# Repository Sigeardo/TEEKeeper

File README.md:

**TEEKeeper** (_Temperature Environment Electronic Keeper_, or _TEEK_ for short) is an open source, Arduino based controller for high temperature electric ovens, such as heat treating ovens for metallurgy/bladesmithing, glass and ceramic kilns, etc.
In a broader sense, this projects aims to develop a platform that can be upgraded, expanded and extended by anyone, bringing more advanced control features to the users.

# Project principles
This university & passion project has been developed with 5 principles in mind:

**1) Open Source and DIY oriented design:**
     TEEK has been inspired by and made possible by many open source and DIY sources, in the forms of documentation, educational material, tools, software, designs etc.
     This project embraces these principles and aspires to give something back to these communities.

**2) Safety and Security:**
     Both in the design of the code and the circuits, developing methods & functions keeping in mind the potential risks for the user.

**3) Accessibility & ease of use:**
     The system may grow more and more complex, but the user must be presented with a simple, undestrandable and intuitive U/I.
     The code must be as readable as possible, to allow anyone to approach the codebase to make 

**4) It doesn't stop at the board:**
     Data logging and analysis tools can help to improve workflows and perform diagnostics checks. Give users data collection methods, statistics and tools.

**6) Be creative & don't be afraid of complexity!**
     But still, try to keep it simple - not trivial!
     
***DISCLAIMER: high temperature & electric related hazards are very real. 
Be aware of what you're doing and use this code at your own risk.***

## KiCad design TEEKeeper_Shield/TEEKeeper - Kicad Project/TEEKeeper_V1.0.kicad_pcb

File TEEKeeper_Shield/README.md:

# TEEKeeper Shield

**TEEKeeper** (_Temperature Environment Electronic Keeper_, or _TEEK_ for short) is an open source, Arduino based controller for high temperature electric ovens, such as heat treating ovens for metallurgy/bladesmithing, glass and ceramic kilns, etc.
In a broader sense, this projects aims to develop a platform that can be upgraded, expanded and extended by anyone, bringing more advanced control features to the users.

This branch contains the KiCad & Gerber source files for the TEEKeeper Shield circuit. The main components are:
> [Arduino Mega2560](https://docs.arduino.cc/hardware/mega-2560/)

> [Adafruit MAX31855K temperature sensor](https://www.adafruit.com/product/269)

> SD card reader w/ 8 pin interface [(example)](https://europe1.discourse-cdn.com/arduino/original/4X/2/f/4/2f487c179e937e868c1862e275f90aaaed0d1cb2.jpeg)

> 3.5" TFT 480x320px ILI9486/HX8357 Screen Mega Shield [LCDWIKI](http://www.lcdwiki.com/3.5inch_Arduino_Display-Mega2560)

> Normally open door switch

> Rotary encoder with push button [Aliexpress](https://it.aliexpress.com/i/32920789846.html)

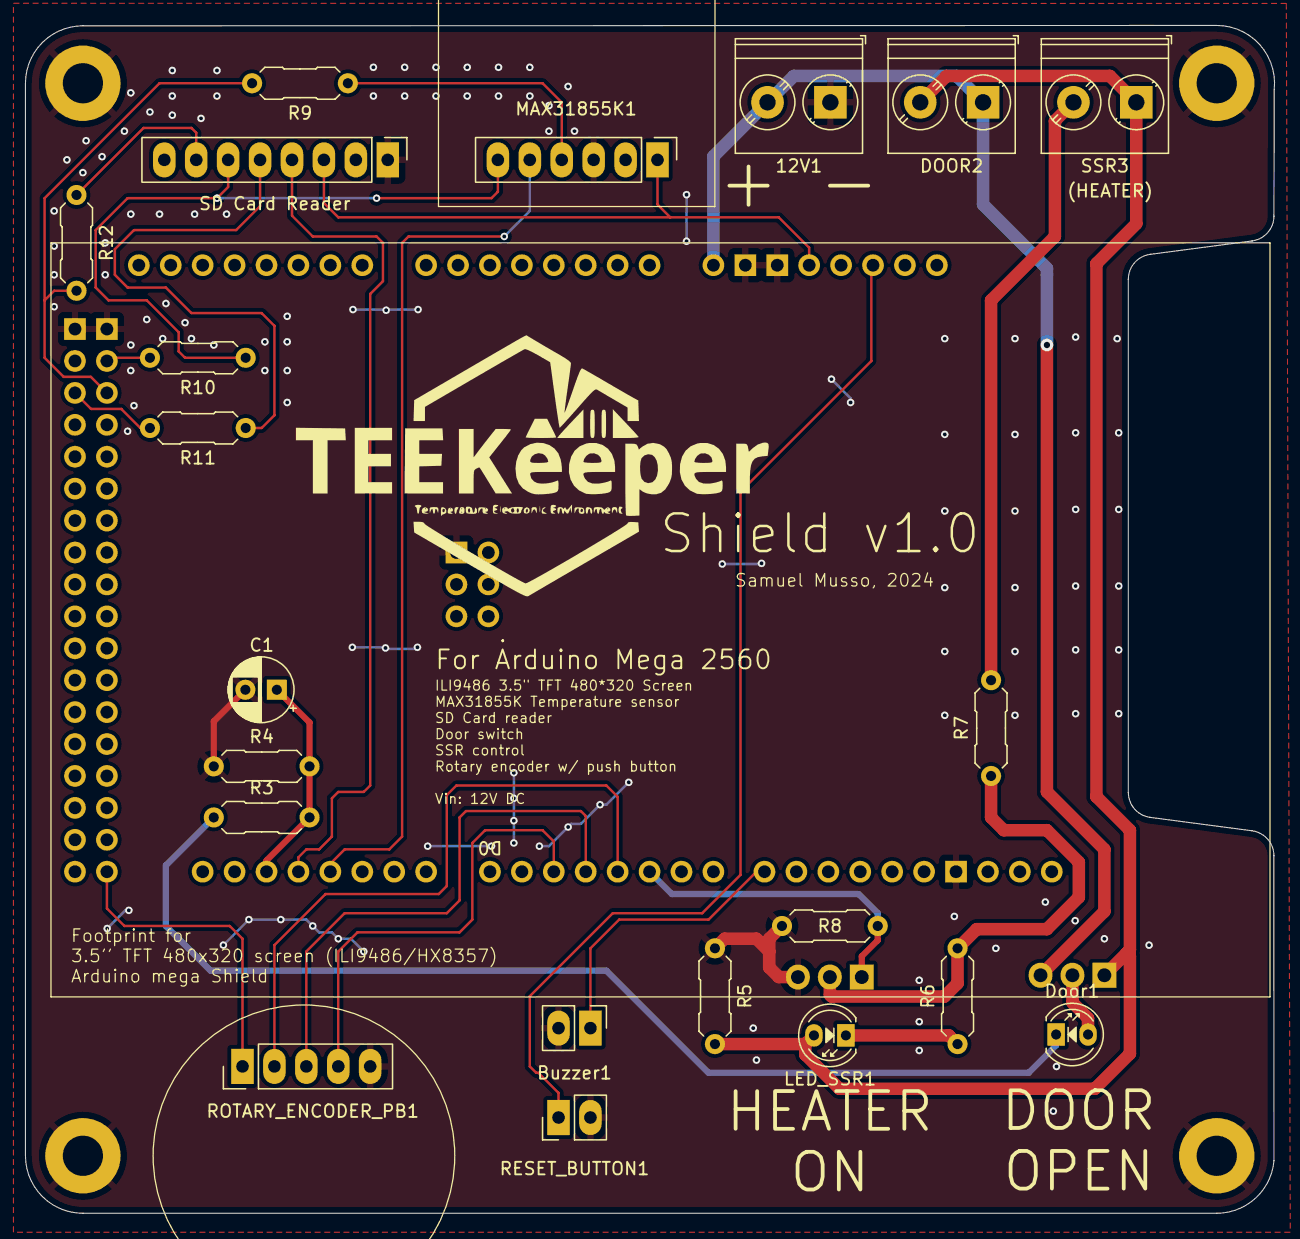
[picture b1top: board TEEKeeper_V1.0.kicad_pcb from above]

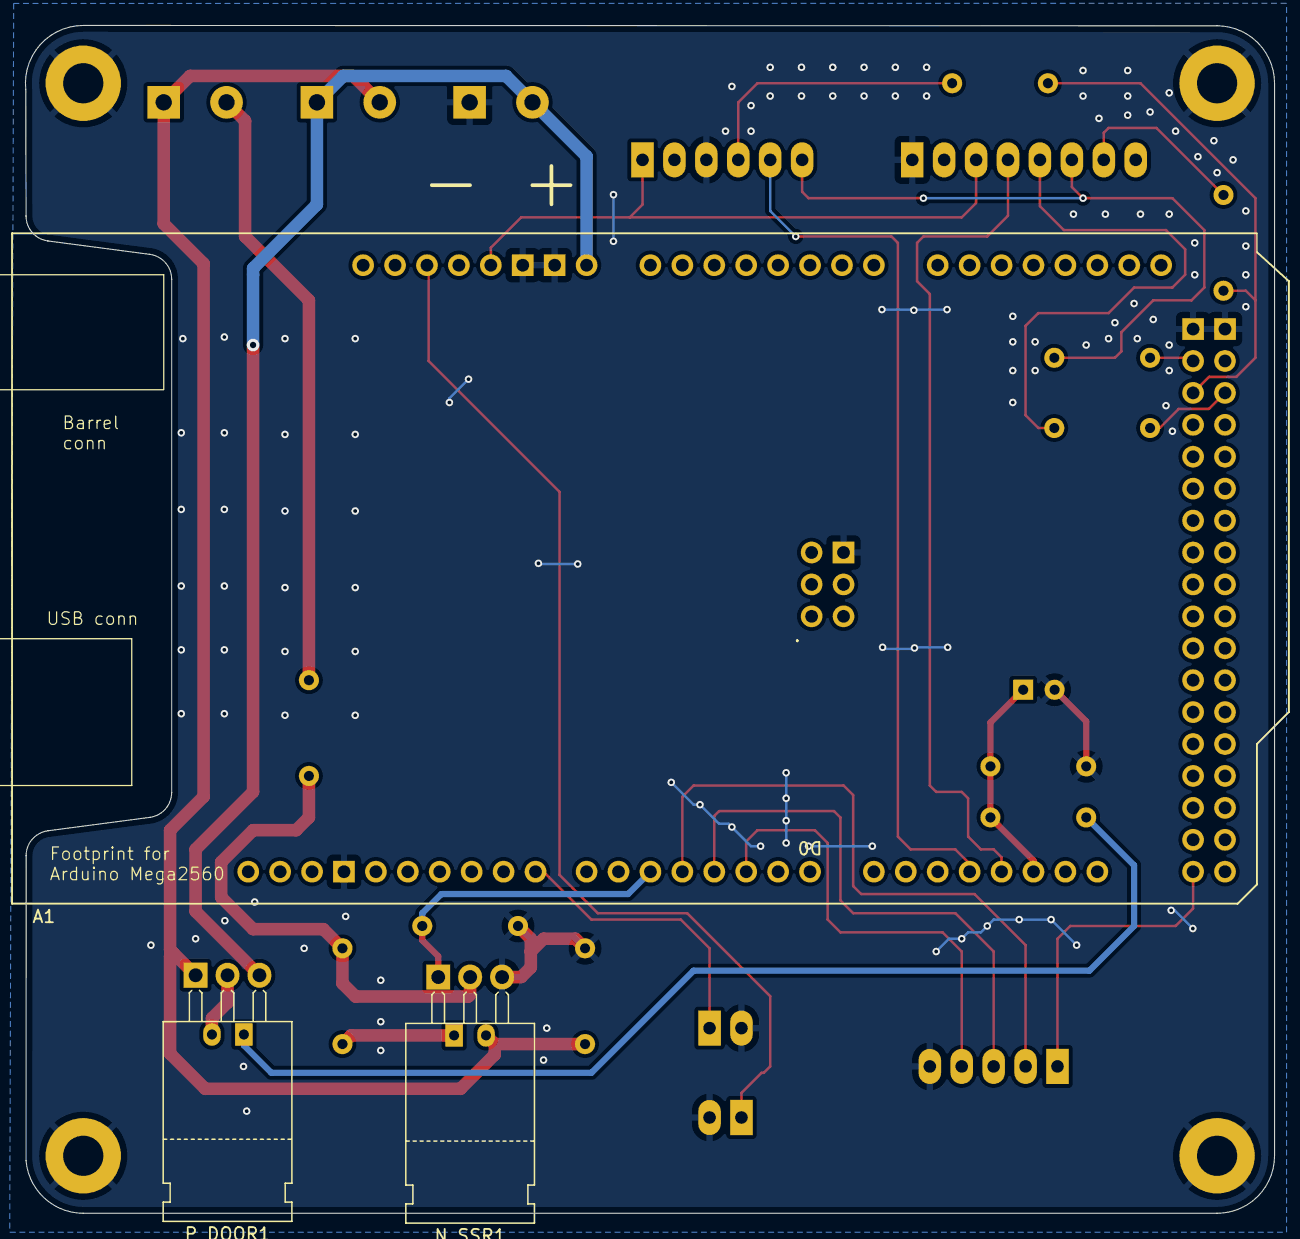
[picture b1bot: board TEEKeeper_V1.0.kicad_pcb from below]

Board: 2 copper layers, 99.4 x 94.5 mm, 28 parts (2 on the bottom side), 25 nets.

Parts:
12V1: Screw_Terminal_2_P5.00mm; TerminalBlock_Phoenix_PT-1,5-2-5.0-H_1x02_P5.00mm_Horizontal
A1: Arduino_Mega2560_R3_Shield
Buzzer1: Buzzer_5V; PinHeader_1x02_P2.54mm_Vertical
C1: 22n; CP_Radial_D5.0mm_P2.50mm
DOOR2: Screw_Terminal_2_P5.00mm; TerminalBlock_Phoenix_PT-1,5-2-5.0-H_1x02_P5.00mm_Horizontal
Door1: LED; LED_D4.0mm
H1, H2, H3, H4: MountingHole_M3_3.2mm_Pad; MountingHole_3.2mm_Pad
LED_SSR1: LED; LED_D4.0mm
MAX31855K1: PINHD_1x6_Female; PinSocket_1x06_P2.54mm_Vertical
N_SSR1: IRFZ44; TO-220-3_Horizontal_TabUp
P_DOOR1: IRF4905; TO-220-3_Horizontal_TabUp
R3, R6: 5k; R_Axial_DIN0207_L6.3mm_D2.5mm_P7.62mm_Horizontal
R4: 3.3k; R_Axial_DIN0207_L6.3mm_D2.5mm_P7.62mm_Horizontal
R5: 100k; R_Axial_DIN0207_L6.3mm_D2.5mm_P7.62mm_Horizontal
R7: 100; R_Axial_DIN0207_L6.3mm_D2.5mm_P7.62mm_Horizontal
R8: 10k; R_Axial_DIN0207_L6.3mm_D2.5mm_P7.62mm_Horizontal
R9, R10, R11, R12: 10; R_Axial_DIN0207_L6.3mm_D2.5mm_P7.62mm_Horizontal
RESET_BUTTON1: PINHD_1x2_Female; PinHeader_1x02_P2.54mm_Vertical
ROTARY_ENCODER_PB1: PINHD_1x5_Female; PinHeader_1x05_P2.54mm_Vertical
SD_CARD1: PINHD_1x8_Female; PinSocket_1x08_P2.54mm_Vertical
SSR3: Screw_Terminal_2_P5.00mm; TerminalBlock_Phoenix_PT-1,5-2-5.0-H_1x02_P5.00mm_Horizontal

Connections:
5V: A1.5V1 (5V), A1.5V3 (5V), MAX31855K1.1, ROTARY_ENCODER_PB1.1, SD_CARD1.3
/System_Shield/Analog_PCB/DOOR_SENS: A1.D19 (D19/RX1), C1.1, R3.2, R4.2
/System_Shield/Analog_PCB/HEATER_CT: A1.D5, N_SSR1.1 (G), R8.2
/System_Shield/Analog_PCB/VIN: 12V1.2, A1.VIN, DOOR2.1, P_DOOR1.3 (S)
/System_Shield/Digital_PCB/BUZ: A1.D8, Buzzer1.1
/System_Shield/Digital_PCB/CLK: MAX31855K1.6, R10.1, SD_CARD1.6
/System_Shield/Digital_PCB/CS_PROBE: A1.D17 (D17/RX2), MAX31855K1.5
/System_Shield/Digital_PCB/CS_SD: A1.D18 (D18/TX1), SD_CARD1.4
/System_Shield/Digital_PCB/D2_INTRR: A1.D2 (D2_INT0), ROTARY_ENCODER_PB1.4
/System_Shield/Digital_PCB/D3_INTRR: A1.D3 (D3_INT1), ROTARY_ENCODER_PB1.3
/System_Shield/Digital_PCB/D4: A1.D4, ROTARY_ENCODER_PB1.2
/System_Shield/Digital_PCB/MISO: A1.D50 (D50_MISO), R9.2, R12.2
/System_Shield/Digital_PCB/MOSI: R11.1, SD_CARD1.5
/System_Shield/Digital_PCB/RESET: A1.RST1 (RESET), RESET_BUTTON1.1
GND: 12V1.1, A1.GND1 (GND), A1.GND2 (GND), A1.GND3 (GND), A1.GND4 (SPI_GND), A1.GND5 (GND), A1.GND6 (GND), Buzzer1.2, C1.2, H1.1, H2.1, H3.1, H4.1, MAX31855K1.3, N_SSR1.3 (S), R4.1, R5.1, R8.1, RESET_BUTTON1.2, ROTARY_ENCODER_PB1.5, SD_CARD1.1
unnamed: A1.D51 (D51_MOSI), R11.2
unnamed: A1.D52 (D52_SCK), R10.2
unnamed: Door1.1, R3.1
unnamed: LED_SSR1.1, R6.1
unnamed: MAX31855K1.4, R9.1
unnamed: N_SSR1.2 (D), R6.2, R7.1
unnamed: Door1.2, P_DOOR1.2 (D)
unnamed: DOOR2.2, LED_SSR1.2, P_DOOR1.1 (G), R5.2, SSR3.1
unnamed: R7.2, SSR3.2
unnamed: R12.1, SD_CARD1.7

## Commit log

2024-12-06 Added Kicad project files
2024-12-06 Uploaded Gerber files
2024-12-06 Added Kicad and Gerber files
2024-12-06 Added readme
2024-12-06 Updated code directory
2024-12-06 Delete TEEKeeper_Alpha/src/experimental directory
    Directory was not meant to be added
2024-12-18 Create LICENSE
2024-12-19 Resolved minor issues
    Fixed broken / bad designed reference connections, fixed pcb courtyard and edges, general cleanup
2024-12-19 Minor footprint fixes
    Changed LED footprints for better accomodate the devices I've been using.
    Fixed some edge cuts issues and refilled zones.
2024-12-22 Fixed minor issues
2024-12-28 Minor adjustments
2024-12-28 Minor changes
2025-01-03 Added connector cutouts
    Added cutouts for the Arduino Mega barrel and USB-A connector.
    Rerouted connections accordingly.
    Added more vias to GND plane along SPI lines and other parallel strips.
    Added clearance for some components.
2025-01-03 Updated gerber files
2025-01-04 Updated code to fit the new shield design
2025-01-04 Folder renamed
2025-01-04 Rename README.md to README.md
2025-01-04 Renamed firmware folder
2025-01-05 updated schematics
2025-01-06 Solved spi hanging issue
2025-01-06 Cleared leftover bits of useless code from debugging
2025-01-07 Updated the ReadTemperature() method to handle critical errors
2025-01-08 fixed Critical Error Screen displaying
2025-01-09 Reworked Arduino Mega clearance
    Due to some clones having their USB and barrel connector placed in slightly different locations, added a big cutout and rerouted tracks accordingly
    uniformed 12V copper lines width
2025-01-23 re-added probe debug mock function
2026-05-26 Restructure: rename firmware and hardware top-level folders
2026-05-26 restructured and corrected bugs
2026-05-26 Ironed out more bugs
